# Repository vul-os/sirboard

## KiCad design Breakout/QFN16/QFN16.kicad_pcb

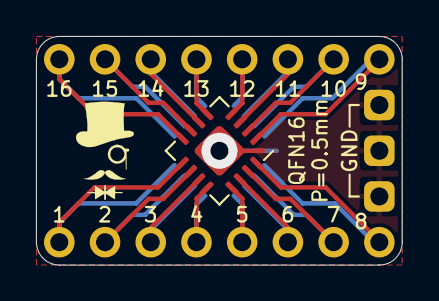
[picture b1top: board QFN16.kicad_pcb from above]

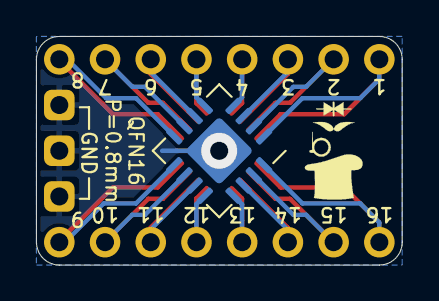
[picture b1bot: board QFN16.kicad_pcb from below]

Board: 2 copper layers, 20.3 x 12.7 mm, 5 parts (2 on the bottom side), 17 nets.

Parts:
J1, J3: Conn_01x08; PinHeader_1x08_P2.54mm_Vertical
J2: Conn_02x08_Counter_Clockwise; QFN-16-1EP_4x4mm_P0.65mm_EP2.1x2.1mm
J4: Conn_02x08_Counter_Clockwise; QFN-16-1EP_5x5mm_P0.8mm_EP2.7x2.7mm
J5: Conn_01x03; PinHeader_1x03_P2.54mm_Vertical

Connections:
unnamed: J1.1, J2.1, J4.8
unnamed: J1.2, J2.2, J4.7
unnamed: J1.3, J2.3, J4.6
unnamed: J1.4, J2.4, J4.5
unnamed: J1.5, J2.5, J4.4
unnamed: J1.6, J2.6, J4.3
unnamed: J1.7, J2.7, J4.2
unnamed: J1.8, J2.8, J4.1
unnamed: J2.9, J3.8, J4.16
unnamed: J2.10, J3.7, J4.15
unnamed: J2.11, J3.6, J4.14
unnamed: J2.12, J3.5, J4.13
unnamed: J2.13, J3.4, J4.12
unnamed: J2.14, J3.3, J4.11
unnamed: J2.15, J3.2, J4.10
unnamed: J2.16, J3.1, J4.9
unnamed: J2.17, J4.17, J5.1, J5.2, J5.3

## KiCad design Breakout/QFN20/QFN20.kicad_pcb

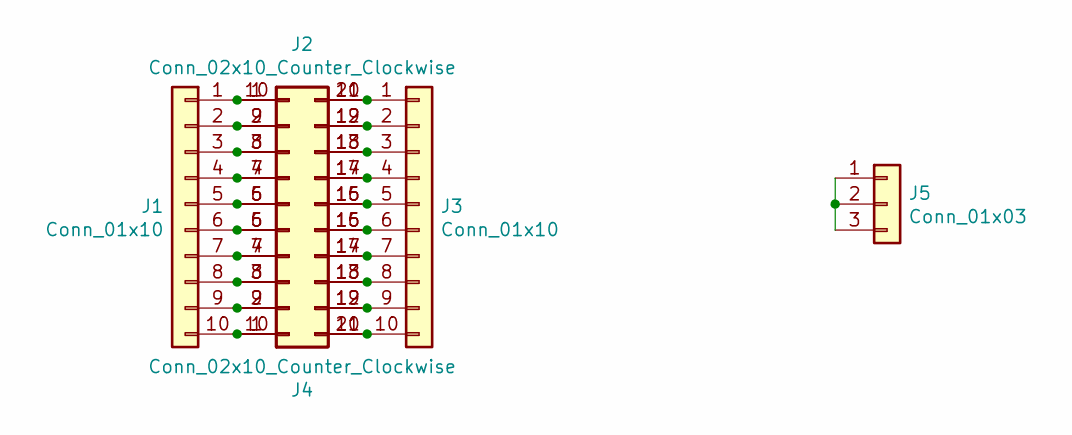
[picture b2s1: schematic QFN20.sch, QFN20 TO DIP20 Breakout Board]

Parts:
J1, J3: Conn_01x10; PinHeader_1x10_P2.54mm_Vertical
J2: Conn_02x10_Counter_Clockwise; QFN-20-1EP_4x4mm_P0.5mm_EP2.5x2.5mm
J4: Conn_02x10_Counter_Clockwise; QFN-20-1EP_5x5mm_P0.65mm_EP3.35x3.35mm
J5: Conn_01x03; PinHeader_1x03_P2.54mm_Vertical

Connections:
unnamed: J1.1, J2.1, J4.10
unnamed: J1.2, J2.2, J4.9
unnamed: J1.3, J2.3, J4.8
unnamed: J1.4, J2.4, J4.7
unnamed: J1.5, J2.5, J4.6
unnamed: J1.6, J2.6, J4.5
unnamed: J1.7, J2.7, J4.4
unnamed: J1.8, J2.8, J4.3
unnamed: J1.9, J2.9, J4.2
unnamed: J1.10, J2.10, J4.1
unnamed: J2.11, J3.10, J4.20
unnamed: J2.12, J3.9, J4.19
unnamed: J2.13, J3.8, J4.18
unnamed: J2.14, J3.7, J4.17
unnamed: J2.15, J3.6, J4.16
unnamed: J2.16, J3.5, J4.15
unnamed: J2.17, J3.4, J4.14
unnamed: J2.18, J3.3, J4.13
unnamed: J2.19, J3.2, J4.12
unnamed: J2.20, J3.1, J4.11
unnamed: J2.21, J4.21, J5.1, J5.2, J5.3

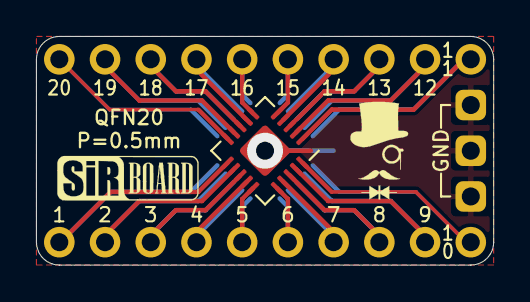
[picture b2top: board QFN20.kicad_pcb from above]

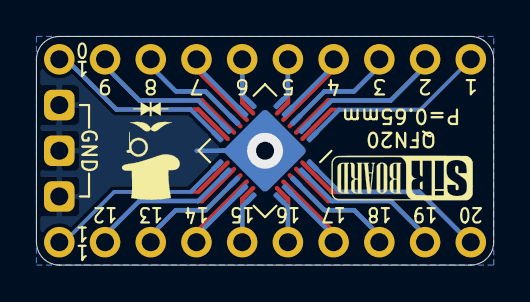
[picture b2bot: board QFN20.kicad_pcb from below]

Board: 2 copper layers, 25.4 x 12.7 mm, 5 parts (2 on the bottom side), 21 nets.

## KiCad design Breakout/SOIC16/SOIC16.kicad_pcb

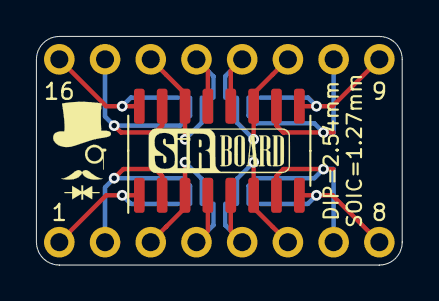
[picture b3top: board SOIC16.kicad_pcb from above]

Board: 2 copper layers, 20.3 x 12.7 mm, 3 parts (0 on the bottom side), 16 nets.

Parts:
J1: Conn_02x08_Counter_Clockwise; SOIC-16_3.9x9.9mm_P1.27mm
J2, J3: Conn_01x08; PinHeader_1x08_P2.54mm_Vertical

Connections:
unnamed: J1.1, J3.1
unnamed: J1.2, J3.2
unnamed: J1.3, J3.3
unnamed: J1.4, J3.4
unnamed: J1.5, J3.5
unnamed: J1.6, J3.6
unnamed: J1.7, J3.7
unnamed: J1.8, J3.8
unnamed: J1.9, J2.8
unnamed: J1.10, J2.7
unnamed: J1.11, J2.6
unnamed: J1.12, J2.5
unnamed: J1.13, J2.4
unnamed: J1.14, J2.3
unnamed: J1.15, J2.2
unnamed: J1.16, J2.1

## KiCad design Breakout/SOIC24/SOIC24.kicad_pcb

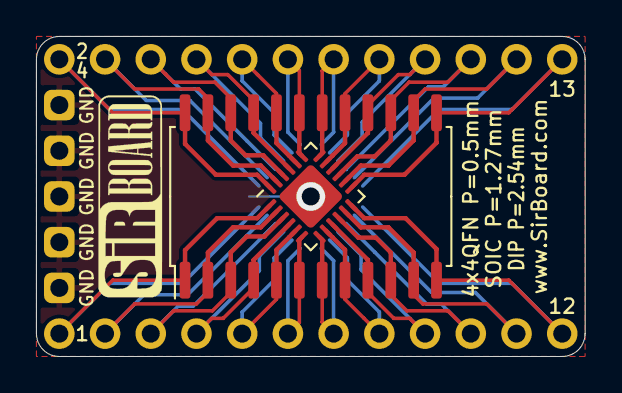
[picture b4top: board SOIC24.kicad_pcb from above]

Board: 2 copper layers, 30.5 x 17.8 mm, 6 parts (1 on the bottom side), 25 nets.

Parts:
J1, J5: Conn_01x12; PinHeader_1x12_P2.54mm_Vertical
J2: Conn_02x12_Counter_Clockwise; QFN-24-1EP_4x4mm_P0.5mm_EP2.6x2.6mm
J3: Conn_02x12_Counter_Clockwise; SOIC-24W_7.5x15.4mm_P1.27mm
J4: Conn_02x12_Counter_Clockwise; QFN-24-1EP_5x5mm_P0.65mm_EP3.4x3.4mm
J6: Conn_01x05; PinHeader_1x05_P2.54mm_Vertical

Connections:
unnamed: J1.1, J2.1, J3.1, J4.24
unnamed: J1.2, J2.2, J3.2, J4.23
unnamed: J1.3, J2.3, J3.3, J4.22
unnamed: J1.4, J2.4, J3.4, J4.21
unnamed: J1.5, J2.5, J3.5, J4.20
unnamed: J1.6, J2.6, J3.6, J4.19
unnamed: J1.7, J2.7, J3.7, J4.18
unnamed: J1.8, J2.8, J3.8, J4.17
unnamed: J1.9, J2.9, J3.9, J4.16
unnamed: J1.10, J2.10, J3.10, J4.15
unnamed: J1.11, J2.11, J3.11, J4.14
unnamed: J1.12, J2.12, J3.12, J4.13
unnamed: J2.13, J3.13, J4.12, J5.12
unnamed: J2.14, J3.14, J4.11, J5.11
unnamed: J2.15, J3.15, J4.10, J5.10
unnamed: J2.16, J3.16, J4.9, J5.9
unnamed: J2.17, J3.17, J4.8, J5.8
unnamed: J2.18, J3.18, J4.7, J5.7
unnamed: J2.19, J3.19, J4.6, J5.6
unnamed: J2.20, J3.20, J4.5, J5.5
unnamed: J2.21, J3.21, J4.4, J5.4
unnamed: J2.22, J3.22, J4.3, J5.3
unnamed: J2.23, J3.23, J4.2, J5.2
unnamed: J2.24, J3.24, J4.1, J5.1
unnamed: J2.25, J4.25, J6.1, J6.2, J6.3, J6.4, J6.5

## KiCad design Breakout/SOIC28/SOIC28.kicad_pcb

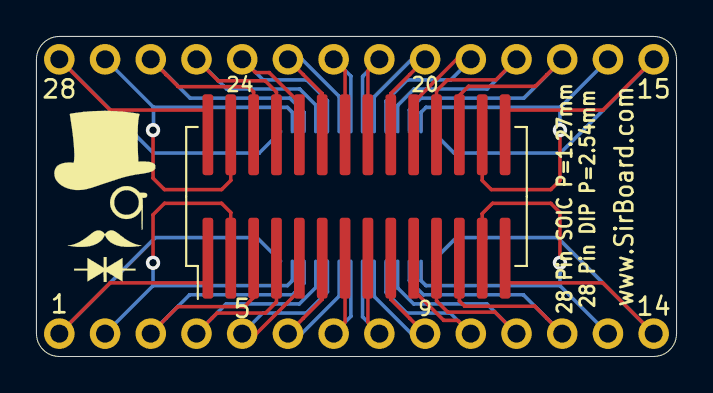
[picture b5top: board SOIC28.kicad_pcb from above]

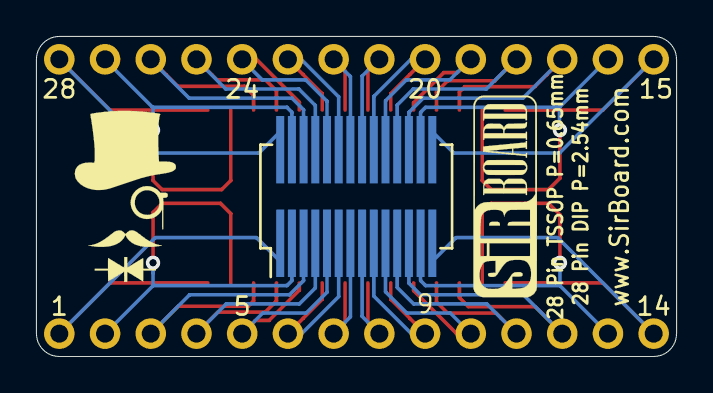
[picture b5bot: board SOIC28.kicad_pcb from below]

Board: 2 copper layers, 35.6 x 17.8 mm, 4 parts (3 on the bottom side), 28 nets.

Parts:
J1, J3: Conn_01x14; PinHeader_1x14_P2.54mm_Vertical
J2: Conn_02x14_Counter_Clockwise; SOIC-28W_7.5x18.7mm_P1.27mm
J4: Conn_02x14_Counter_Clockwise; SSOP-28_5.3x10.2mm_P0.65mm

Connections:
unnamed: J1.1, J2.1, J4.14
unnamed: J1.2, J2.2, J4.13
unnamed: J1.3, J2.3, J4.12
unnamed: J1.4, J2.4, J4.11
unnamed: J1.5, J2.5, J4.10
unnamed: J1.6, J2.6, J4.9
unnamed: J1.7, J2.7, J4.8
unnamed: J1.8, J2.8, J4.7
unnamed: J1.9, J2.9, J4.6
unnamed: J1.10, J2.10, J4.5
unnamed: J1.11, J2.11, J4.4
unnamed: J1.12, J2.12, J4.3
unnamed: J1.13, J2.13, J4.2
unnamed: J1.14, J2.14, J4.1
unnamed: J2.15, J3.14, J4.28
unnamed: J2.16, J3.13, J4.27
unnamed: J2.17, J3.12, J4.26
unnamed: J2.18, J3.11, J4.25
unnamed: J2.19, J3.10, J4.24
unnamed: J2.20, J3.9, J4.23
unnamed: J2.21, J3.8, J4.22
unnamed: J2.22, J3.7, J4.21
unnamed: J2.23, J3.6, J4.20
unnamed: J2.24, J3.5, J4.19
unnamed: J2.25, J3.4, J4.18
unnamed: J2.26, J3.3, J4.17
unnamed: J2.27, J3.2, J4.16
unnamed: J2.8, J3.1, J4.15

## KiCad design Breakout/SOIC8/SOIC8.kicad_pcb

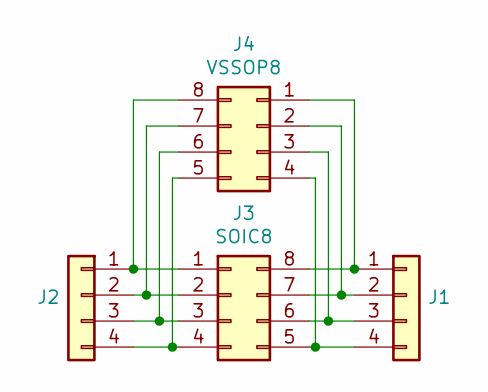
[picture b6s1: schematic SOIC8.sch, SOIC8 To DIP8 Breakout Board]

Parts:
J1, J2: Conn_01x04; PinHeader_1x04_P2.54mm_Vertical
J3: SOIC8; SOIC-8_3.9x4.9mm_P1.27mm
J4: VSSOP8; VSSOP-8_2.3x2mm_P0.5mm

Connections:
unnamed: J1.1, J3.8, J4.1
unnamed: J1.2, J3.7, J4.2
unnamed: J1.3, J3.6, J4.3
unnamed: J1.4, J3.5, J4.4
unnamed: J2.1, J3.1, J4.8
unnamed: J2.2, J3.2, J4.7
unnamed: J2.3, J3.3, J4.6
unnamed: J2.4, J3.4, J4.5

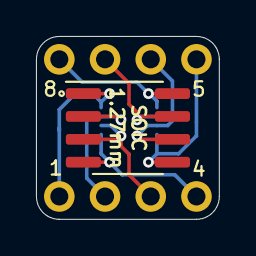
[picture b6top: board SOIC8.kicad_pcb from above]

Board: 2 copper layers, 10.2 x 10.2 mm, 4 parts (1 on the bottom side), 8 nets.
